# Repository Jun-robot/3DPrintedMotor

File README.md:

# 3DPrintedMotor

## Overview
3Dプリンタで作る自作モーターのリポジトリです。

アイデアがより的確に実現できるようになるといいなと思って開発中です。

## How to make
#### 必要なもの
- 3Dプリンタ
- ネジとかコイルとかベアリングとか

#### 作り方
1. "3Dmodels"の中にある5つのSTLファイルをダウンロード！！
1. 3Dプリンタで印刷！！
1. コイル巻いたり、組み立てたり
   - 必要な部品の型番は今後、追記していきます。
	 - 今のところ、設計データから推定できます。

## Concept
- 3Dプリンタさえあれば手に入る
  - あとは、ネジやコイルの規格品のみで作成可能！
- 開発物に適した形状、性能に。
  - アイデアの妥協をなくし、作りたいモノに最適化

## Mechanism
Fusion360で作成

https://a360.co/3StNydJ

## Circuit
KiCADで設計

DRV8332とSTM32F446を使用した自作基板

磁気エンコーダーはAS5601を使用

## Software
VScode + PlatformIOでArduinoで開発

現在は、強制転流。
今後フィードバック制御をかけていく予定

## Achievement
- サイエンスキャッスル2022関東大会 口頭発表
- [未踏ジュニア2023採択](https://jr.mitou.org/projects/2023/3d_printed_brushless_motor)
- MakerFaireTokyo2023 未踏ジュニアブースにて展示
- 未踏ジュニア成果報告会2023 発表

## Licence
MIT

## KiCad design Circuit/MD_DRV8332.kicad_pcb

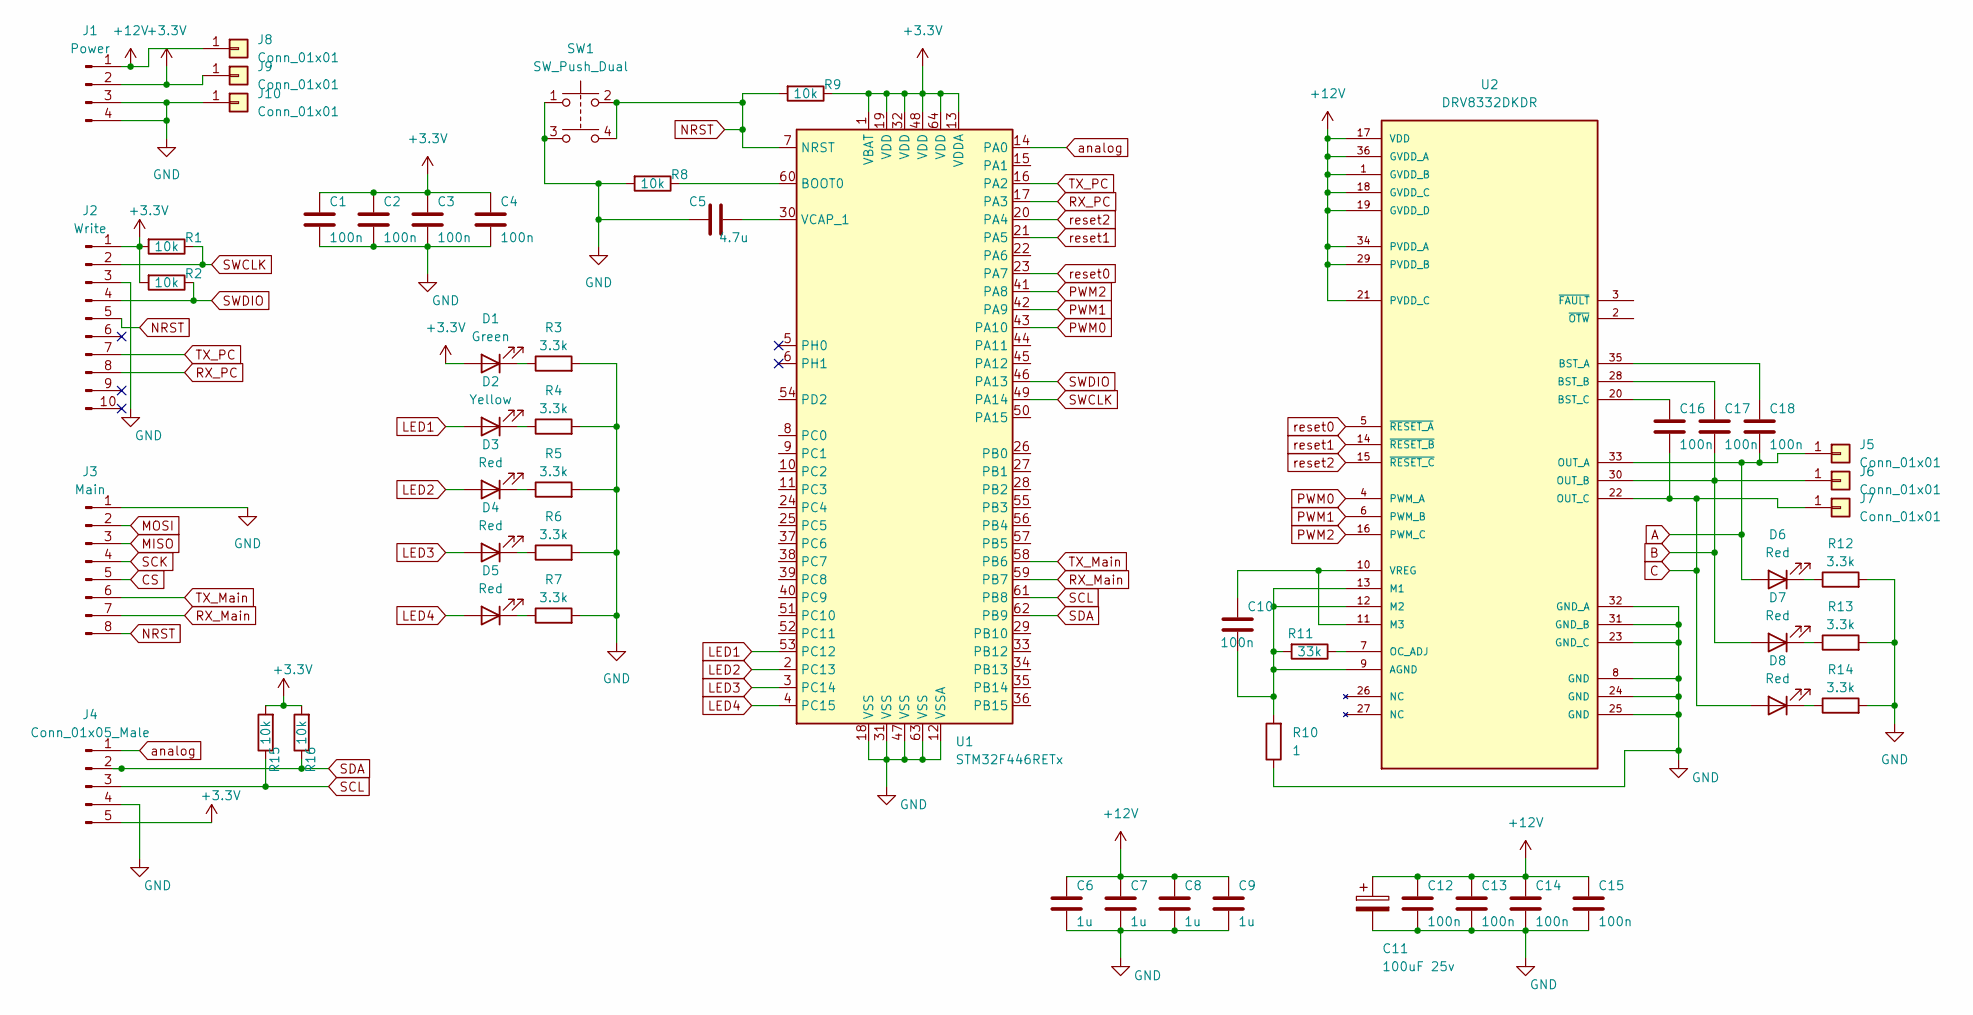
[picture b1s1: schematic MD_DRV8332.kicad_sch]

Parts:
C1, C2, C3, C4, C10, C12, C13, C14, C15, C16, C17, C18: 100n; C_0603_1608Metric_Pad1.08x0.95mm_HandSolder; LCSC C307331
C5: 4.7u; C_0603_1608Metric_Pad1.08x0.95mm_HandSolder; LCSC C23733
C6, C7, C8, C9: 1u; C_0603_1608Metric_Pad1.08x0.95mm_HandSolder; LCSC C52923
C11: 100uF 25v; CP_Radial_D5.0mm_P2.00mm
D1: Green; D_0603_1608Metric_Pad1.05x0.95mm_HandSolder; LCSC C72043
D2: Yellow; D_0603_1608Metric_Pad1.05x0.95mm_HandSolder; LCSC C72038
D3, D4, D5, D6, D7, D8: Red; D_0603_1608Metric_Pad1.05x0.95mm_HandSolder; LCSC C2286
J1: Power; Molex_SPOX_5267-04A_1x04_P2.50mm_Vertical
J2: Write; IDC-Header_2x05_P2.54mm_Horizontal
J3: Main; Molex_SPOX_5267-08A_1x08_P2.50mm_Vertical
J4: Conn_01x05_Male; Molex_SPOX_5267-05A_1x05_P2.50mm_Vertical
J5, J6, J7, J8, J9: Conn_01x01; TestPoint_THTPad_D4.0mm_Drill2.0mm
J10: Conn_01x01; TestPoint_THTPad_4.0x4.0mm_Drill2.0mm
R1, R2, R8, R9, R15, R16: 10k; R_0603_1608Metric_Pad0.98x0.95mm_HandSolder; LCSC C25744
R3, R4, R5, R6, R7, R12, R13, R14: 3.3k; R_0603_1608Metric_Pad0.98x0.95mm_HandSolder; LCSC C25890
R10: 1; R_0603_1608Metric_Pad0.98x0.95mm_HandSolder; LCSC C25086
R11: 33k; R_0603_1608Metric_Pad0.98x0.95mm_HandSolder; LCSC C25792
SW1: SW_Push_Dual; TACT2; LCSC C318884
U1: STM32F446RETx; LQFP-64_10x10mm_P0.5mm; LCSC C69336
U2: DRV8332DKDR; HTSSOP36; PARTREV G

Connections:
+3.3V: C1.1, C2.1, C3.1, C4.1, D1.2 (A), J1.2, J2.1, J4.5, J9.1, R1.2, R2.2, R9.1, R15.2, R16.2, U1.1 (VBAT), U1.13 (VDDA), U1.19 (VDD), U1.32 (VDD), U1.48 (VDD), U1.64 (VDD)
+12V: C6.1, C7.1, C8.1, C9.1, C11.1, C12.1, C13.1, C14.1, C15.1, J1.1, J8.1, U2.1 (GVDD_B), U2.17 (VDD), U2.18 (GVDD_C), U2.19 (GVDD_D), U2.21 (PVDD_C), U2.29 (PVDD_B), U2.34 (PVDD_A), U2.36 (GVDD_A)
A: C18.2, D6.2 (A), J5.1, U2.33 (OUT_A)
B: C17.2, D7.2 (A), J6.1, U2.30 (OUT_B)
C: C16.2, D8.2 (A), J7.1, U2.22 (OUT_C)
CS: J3.5
GND: C1.2, C2.2, C3.2, C4.2, C5.1, C6.2, C7.2, C8.2, C9.2, C11.2, C12.2, C13.2, C14.2, C15.2, J1.3, J1.4, J2.3, J3.1, J4.4, J10.1, R3.2, R4.2, R5.2, R6.2, R7.2, R8.2, R10.1, R12.2, R13.2, R14.2, SW1.1, SW1.3, U1.12 (VSSA), U1.18 (VSS), U1.31 (VSS), U1.47 (VSS), U1.63 (VSS), U2.8 (GND), U2.23 (GND_C), U2.24 (GND), U2.25 (GND), U2.31 (GND_B), U2.32 (GND_A)
LED1: D2.2 (A), U1.53 (PC12)
LED2: D3.2 (A), U1.2 (PC13)
LED3: D4.2 (A), U1.3 (PC14)
LED4: D5.2 (A), U1.4 (PC15)
MISO: J3.3
MOSI: J3.2
NRST: J2.5, J3.8, R9.2, SW1.2, SW1.4, U1.7 (NRST)
unnamed: C5.2, U1.30 (VCAP_1)
unnamed: C10.1, U2.10 (VREG), U2.11 (M3)
unnamed: C10.2, R10.2, R11.2, U2.9 (AGND), U2.12 (M2), U2.13 (M1)
unnamed: C16.1, U2.20 (BST_C)
unnamed: C17.1, U2.28 (BST_B)
unnamed: C18.1, U2.35 (BST_A)
unnamed: D1.1 (K), R3.1
unnamed: D2.1 (K), R4.1
unnamed: D3.1 (K), R5.1
unnamed: D4.1 (K), R6.1
unnamed: D5.1 (K), R7.1
unnamed: D6.1 (K), R12.1
unnamed: D7.1 (K), R13.1
unnamed: D8.1 (K), R14.1
unnamed: R8.1, U1.60 (BOOT0)
unnamed: R11.1, U2.7 (OC_ADJ)
PWM0: U1.43 (PA10), U2.4 (PWM_A)
PWM1: U1.42 (PA9), U2.6 (PWM_B)
PWM2: U1.41 (PA8), U2.16 (PWM_C)
RX_Main: J3.7, U1.59 (PB7)
RX_PC: J2.8, U1.17 (PA3)
SCK: J3.4
SCL: J4.3, R15.1, U1.61 (PB8)
SDA: J4.2, R16.1, U1.62 (PB9)
SWCLK: J2.2, R1.1, U1.49 (PA14)
SWDIO: J2.4, R2.1, U1.46 (PA13)
TX_Main: J3.6, U1.58 (PB6)
TX_PC: J2.7, U1.16 (PA2)
analog: J4.1, U1.14 (PA0)
reset0: U1.23 (PA7), U2.5 (~RESET_A)
reset1: U1.21 (PA5), U2.14 (~RESET_B)
reset2: U1.20 (PA4), U2.15 (~RESET_C)

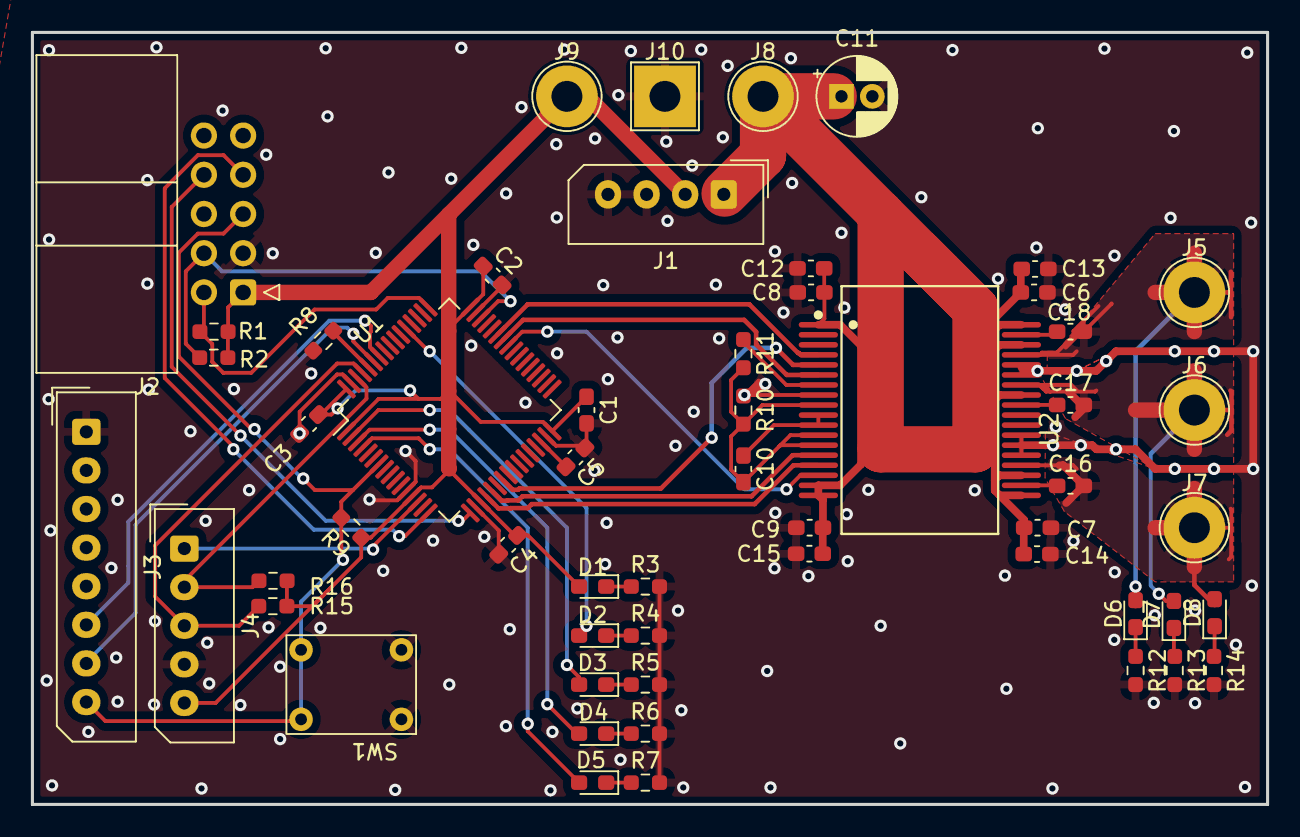
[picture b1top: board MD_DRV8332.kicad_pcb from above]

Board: 2 copper layers, 80.0 x 50.0 mm, 55 parts (0 on the bottom side), 42 nets.

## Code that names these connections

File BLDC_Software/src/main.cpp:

#include <Arduino.h>

void setup() {
  pinMode(PC12, OUTPUT);

	pinMode(PA10,OUTPUT);
	pinMode(PA9,OUTPUT);
	pinMode(PA8,OUTPUT);

	pinMode(PA7,OUTPUT);
	pinMode(PA5,OUTPUT);
	pinMode(PA4,OUTPUT);
	digitalWrite(PA7, HIGH);
	digitalWrite(PA5, HIGH);
	digitalWrite(PA4, HIGH);

	digitalWrite(PC12, HIGH);
	//Serial.begin(115200);
	//Serial.println("Hello World!");
	analogWriteFrequency(20000);
	}


float i = 0;
void loop() {
	int U, V, W = 0;
	U = (sin(i)+1 )* 127;
	V = (sin(i+ 2*PI/3)+1 )* 127;
	W = (sin(i+ 4*PI/3)+1 )* 127;
	// i = i + 0.11; //既製品+乾電池  
	// i = i + 0.003; //自作+Lipo
	//i = i + 0.0025;
	i = i + 0.0078;

	analogWrite(PA10, U);
	analogWrite(PA9, V);
	analogWrite(PA8, W);
}

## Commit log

2023-11-03 画像追加
2023-11-03 モデルの変更
2023-11-03 画像小さくしたよ
2023-11-03 見た目良くした
2023-11-03 詳細追加
2023-11-03 スペルミス修正
2023-11-03 ちょっと追記
2023-11-04 資料追加
